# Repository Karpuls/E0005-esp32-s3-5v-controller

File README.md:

# E0005: ESP32-S3 5 V controller board

The 5 V version of the E0003 control-box mainboard. An **ESP32-S3** runs the box from a **2S1P 21700 pack** (Molicel P50B, holders on the bottom side), or from **plain 5 V USB-C (no PD)** with no cells fitted. One protected **5 V system rail (V5)** feeds the 3V3 regulator and five **+5 V peripheral ports**:
- 4 × fader driver (E0001 pinout);
- 1 × haptic knob (E0002 pinout).

Each port has its own eFuse and an I²C channel through a mux. The board also drives an **EYESPI SPI LCD** and reads **4 switch inputs**.

The current E0001 rev C and E0002 rev B need 6–9 V. They **will not run** on E0005: 5 V revisions are needed (SPEC §6 is their host-interface spec).

*Top side (KiCad 3D render):*
- *USB-C J11, the U_IN eFuse, the BQ25887 charger and the TPS56637 buck on the west side;*
- *the five JST-GH ports with their eFuses along the north edge;*
- *the ESP32-S3 module with its antenna keep-out at the east edge;*
- *switch inputs, power button, EYESPI and BOOT/RESET on the south edge.*

## Key specs
| | |
|---|---|
| Board | **Rev A**, 125 × 73 mm, R3 corners, 4 × M3 (Ø3.2 mm plated, 4 mm inset) |
| PCB | **4 layers, 1.6 mm**, 1 oz outer / 0.5 oz inner, JLC impedance stackup **JLC04161H-3313**. USB pair 90 Ω differential (W 0.153 / S 0.20 mm, coplanar, L1 over In1 GND) |
| Layers | **F.Cu**: parts, signals, power pours · **In1**: solid GND · **In2**: V5 plane (west column + port band), 3V3 plane, short slow lanes · **B.Cu**: signals, GND pour, holder lugs, V5 strap |
| MCU | **ESP32-S3-WROOM-1-N16R2** (16 MB flash, 2 MB PSRAM, Wi-Fi/BLE, PCB antenna) |
| Battery | **2 × Molicel P50B 21700 in series** (2S1P, ≈ 36 Wh), 2 × Keystone 1121 holders on the bottom |
| USB | **USB-C, 5 V only, no PD:** 2 × 5.1 kΩ Rd, CC1/CC2 to the ESP32 ADC to read the source's Rp level. Native USB for flashing, CDC and JTAG |
| Charger | **TI BQ25887** 2 A boost charger (5 V → 2S), I²C, 16-bit ADC, integrated cell balancing |
| 5 V rail (V5) | Diode-OR by voltage: **USB through a TPS259470A eFuse** (0.50 / 1.37 / 2.81 A limit, chosen by firmware) **or** the **TPS56637 6 A buck** from the pack (4.80 V). Copper is sized for 4.6 A at ΔT ≤ 20 °C |
| Ports | **6 × TPS259470A** eFuses in total: U_IN plus one per port J1–J5 (OVLO 6.0 V, UVLO 3.8 V, reverse blocking, auto-retry) |
| Status | DRC 0 errors / 0 unconnected / 0 parity (U1 library exception only), ERC 0. Fab outputs in `fab/E0005_revA/`. See "Status and open items" |

## Features and interfaces
| Function | Implementation |
|---|---|
| USB-C (J11) | ESP32-S3 native USB (flashing, CDC console, JTAG) and the charging input. Runs the whole system with no battery fitted. SMF9.0A TVS on VBUS, USBLC6 ESD on the data lines |
| Power path | **U_IN** (TPS259470A) feeds V5 from VBUS. Its limit is 0.50 A at reset, and 1.37 A or 2.81 A when firmware selects it from the CC level. When the load exceeds the USB limit, the **TPS56637** buck makes up the difference from the battery. U_IN blocks reverse current, so the buck never back-feeds the USB host |
| Charger | **BQ25887** 5 V → 2S boost charger, 2 A, balancing ≈ 110 mA, cell OVP, JEITA (NTCs RT1/RT2) |
| Battery management | **MAX17205** fuel gauge (5 mΩ sense, Kelvin) · **S-8252** 2S protector with 2 × PSMN2R0-30YLDX · **10 A fuse F1** · per-cell voltages from the BQ25887 ADC |
| 3V3 rail | TPS629210 1 A buck from V5, so a port fault never resets the MCU |
| Ports J1–J4 | 4 × E0001-pinout ports, JST-GH 4-pin (1 +5V, 2 SCL, 3 SDA, 4 GND), eFuse 0.74–1.00 A, SMF5.0A TVS |
| Port J5 | 1 × E0002-pinout port, JST-GH 6-pin (1–2 +5V, 3 SCL, 4 SDA, 5–6 GND), eFuse 1.80–2.20 A |
| I²C | **I2C0** on-board: BQ25887, MAX17205, TCA9535 expander. **I2C1**: PCA9548A mux, one channel per port, 3.3 V pull-ups, ESD and series resistors |
| LCD (J10) | 18-pin 0.5 mm **EYESPI** FPC for the Adafruit 2.0" 320×240 IPS (PID 4311) |
| Switch inputs (J6–J9) | 4 × JST-GH 2-pin, pull-up + RC + ESD, wake from deep sleep |
| Buttons | Power button (on board, plus JST-GH J12 for a panel button) with a **soft power latch on the buck EN** ("off" ≈ 35 µA); BOOT, RESET |
| Silkscreen | **"5V Jn E0001"** / **"5V J5 E0002"** at each port |
| Test points | None (owner rule). Bring-up is via USB and component pads |

## Power architecture
- **USB only:** V5 = VBUS through U_IN, at 4.9–5.1 V. The buck is off.
- **Battery only:** V5 = TPS56637 output, 4.80 V. Firmware sheds the ports below a 6.4 V pack.
- **USB + battery:** USB holds V5 above the buck set point, so the buck is idle. When the load exceeds U_IN's limit, U_IN regulates its current and the buck carries the rest. The charger charges the pack from VBUS at the same time; firmware keeps U_IN + charger input within the source's Rp budget.
- Load budget:
  - worst plausible V5 load 4.85 A;
  - firmware port budget 4.4 A;
  - TPS56637 rated 6 A, with a 6.3–8.6 A valley limit.
- Details: [`docs/SPEC.md`](docs/SPEC.md) §5.

## Copper layers
All four layers are seen from the top, with the board outline (KiCad plots).

| | |
|---|---|
|  *F.Cu: parts, signals, power pours* |  *In1.Cu: solid GND reference plane* |
|  *In2.Cu: V5 plane (west column, port band), 3V3 plane* |  *B.Cu: signals, GND pour, holder lugs, V5 strap* |

## More views
| | |
|---|---|
|  *Bottom side: the two Keystone 1121 holders* |  *Top mask and silk, rendered from the gerbers* |

## Repository layout
| Path | Content |
|---|---|
| `E0005_controller.kicad_pro` / `.kicad_pcb` / `.kicad_sch` | KiCad project, board and root schematic |
| `power.kicad_sch`, `battery.kicad_sch`, `mcu.kicad_sch`, `ports.kicad_sch` | Schematic sheets: USB-C, U_IN, charger, buck and 3V3 · battery pack, protection and gauge · ESP32-S3, LCD, switches, buttons · peripheral ports |
| `E0005_controller.kicad_dru` | JLC design rules, the no-via-on-pad rule, and the routing pour/USB rules |
| `docs/SPEC.md` | Requirements and architecture spec (v1.4, frozen) |
| `docs/schematic_notes.md`, `docs/placement_notes.md`, `docs/routing_notes.md` | Capture notes (deviations, V5 capacitance, back-feed), placement notes, routing notes (widths, IPC-2152 table, USB, hot loops) |
| `docs/images/` | Board and 3D renders used here |
| `bom/` | DigiKey BOM (`E0005_digikey_bom.csv`, generated), new-part lookups, sourcing notes |
| `lib/` | Project symbols and footprints (`E0005.*`), the board outline and holes (`E0005_board`), and mechanical parts with 3D models (`E0005_mech.*`) |
| `build/scripts/` | Generators and checks. **`fab_export.sh`** builds the fab package; **`gerber_review.py`** renders and measures the gerbers; `make_bom.py` builds the BOM |
| `build/route/` | Hand-routing scripts (sent over KiCad IPC; no autorouter) |
| `fab/E0005_revA/` | **Fabrication package:** `E0005_revA_gerbers_JLC.zip` (upload to JLC), gerbers, drill, placement, assembly PDFs, BOM, STEP, DRC/ERC reports, gerber review, [README](fab/E0005_revA/README.md) with the order settings, and [PREORDER.md](fab/E0005_revA/PREORDER.md) |

## Status and open items
- **Rev A fab outputs are generated:** DRC 0 / 0 / 0 (U1 `lib_footprint_mismatch` accepted), ERC 0. JLC order settings (JLC04161H-3313 with impedance control, tented vias, ENIG) are in [`fab/E0005_revA/README.md`](fab/E0005_revA/README.md).
- **Before ordering** ([`PREORDER.md`](fab/E0005_revA/PREORDER.md)):
  - Test-fit the flat-top P50B in the Keystone 1121.
  - Confirm the DigiKey cut-tape PNs for BQ25887RGER and TPS56637RPAR.
  - Order the LCSC / Adafruit / nkon parts.
- **Bench checks at bring-up:**
  - O-1: TPS56637 load step (FF C79 100 → 220 pF if it rings);
  - O-2b: TPS56637 temperature with the SW discharge active (USB only, no battery);
  - O-4: USB-unplug V5 dip at full load, and U_IN temperature in current limit.
- **Sister boards:** E0001 and E0002 need 5 V revisions to work on this board (out of scope here).

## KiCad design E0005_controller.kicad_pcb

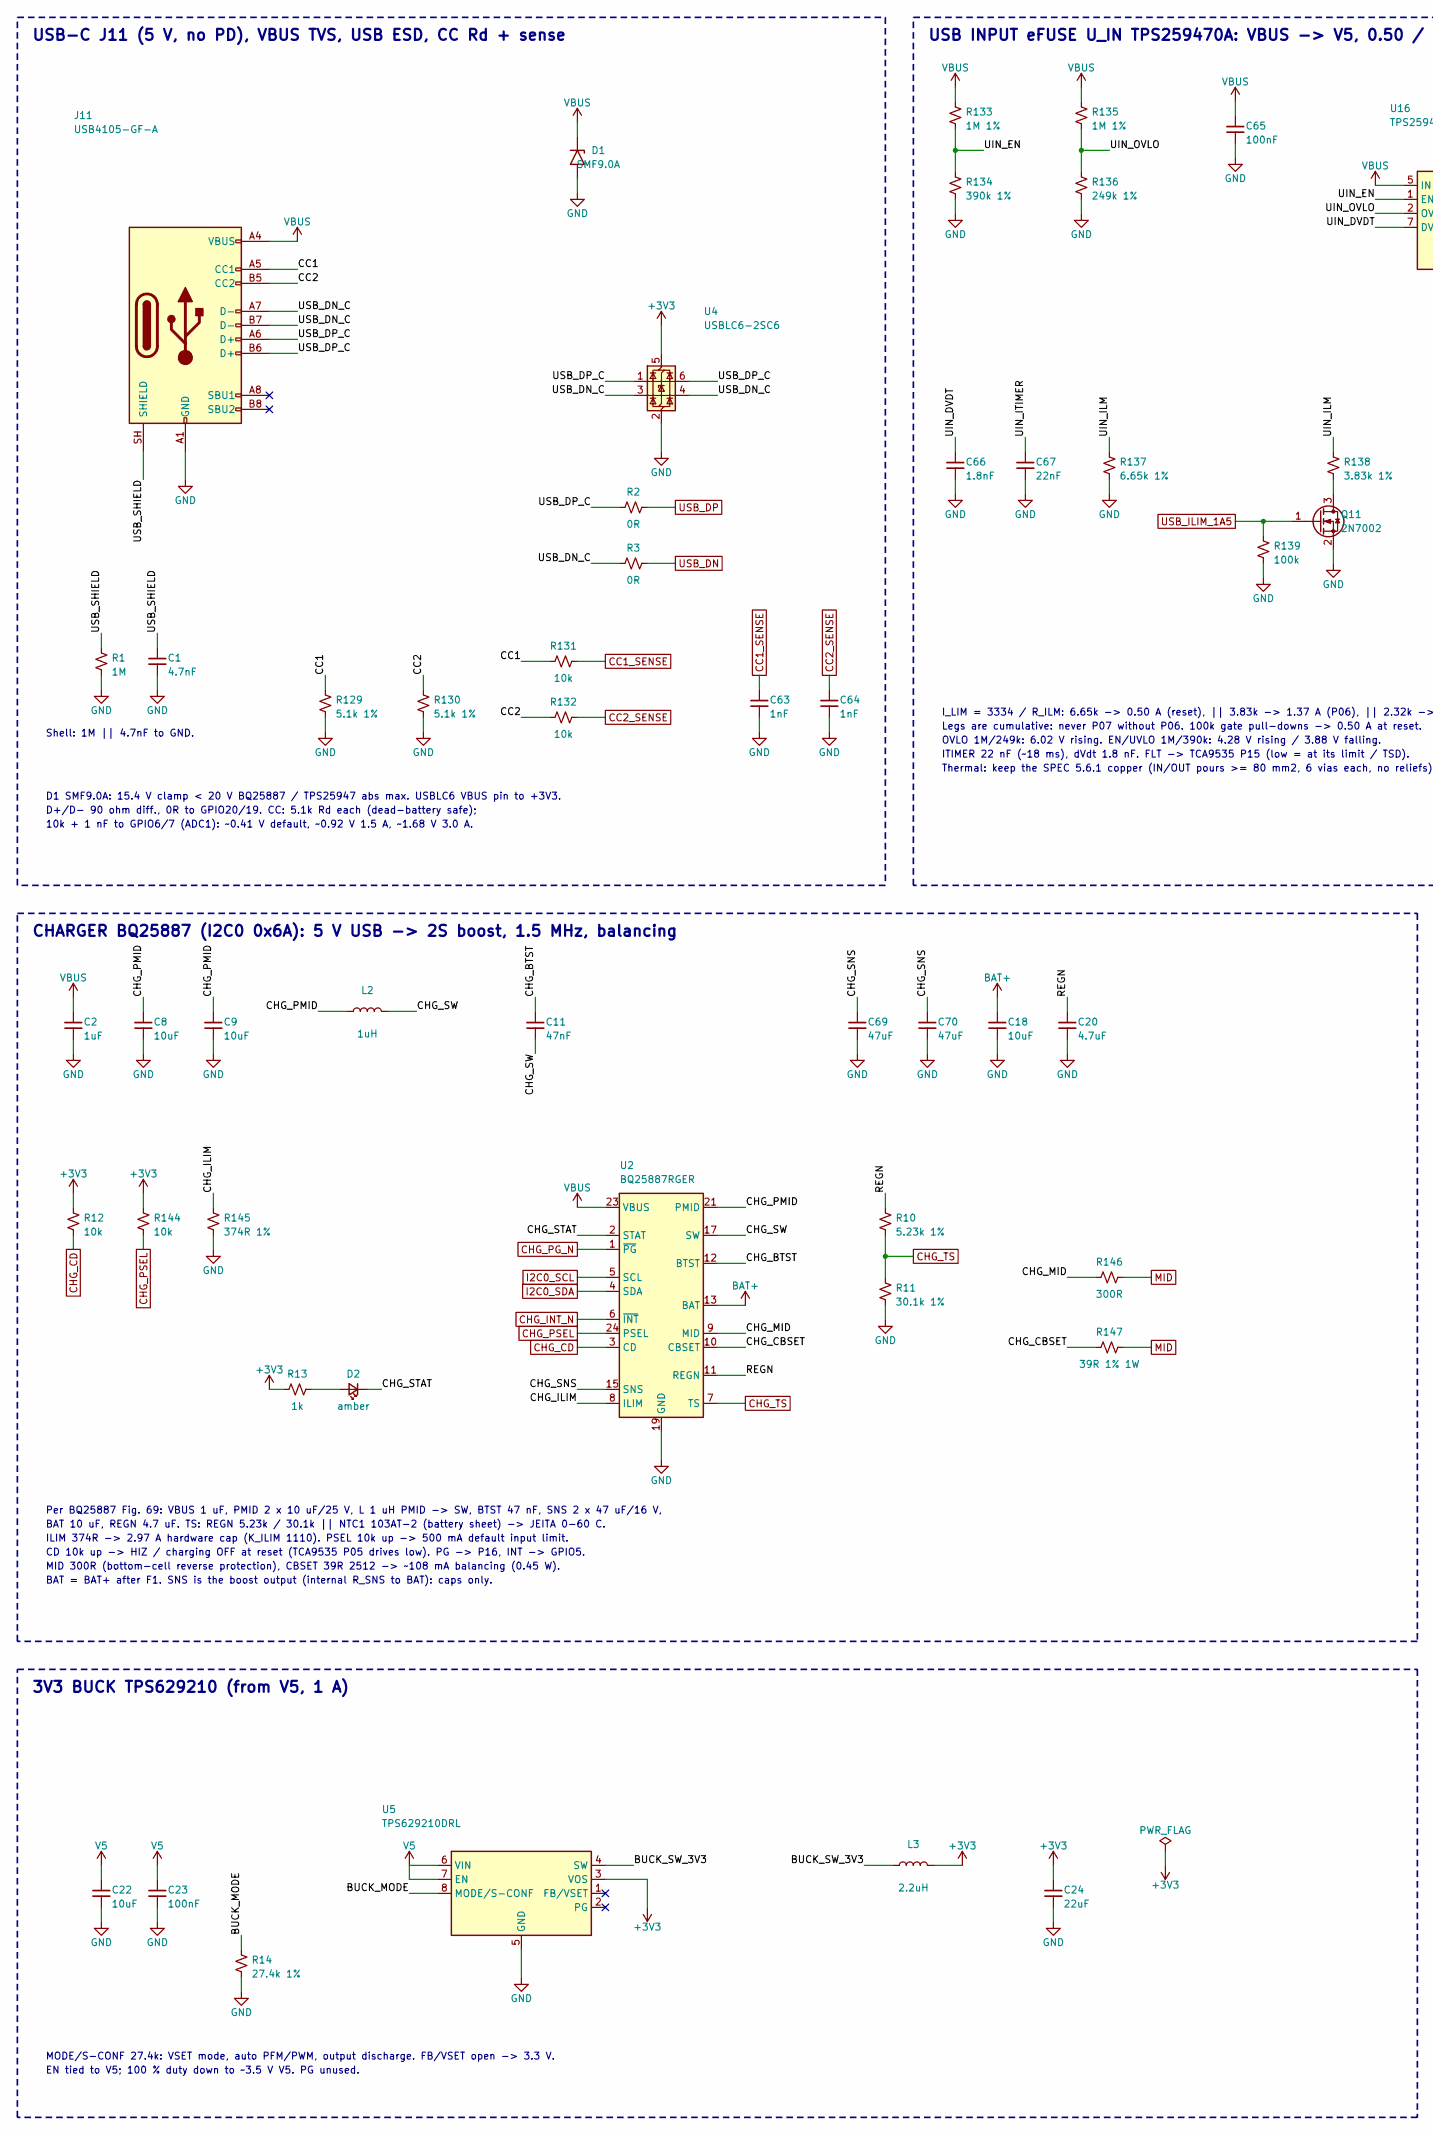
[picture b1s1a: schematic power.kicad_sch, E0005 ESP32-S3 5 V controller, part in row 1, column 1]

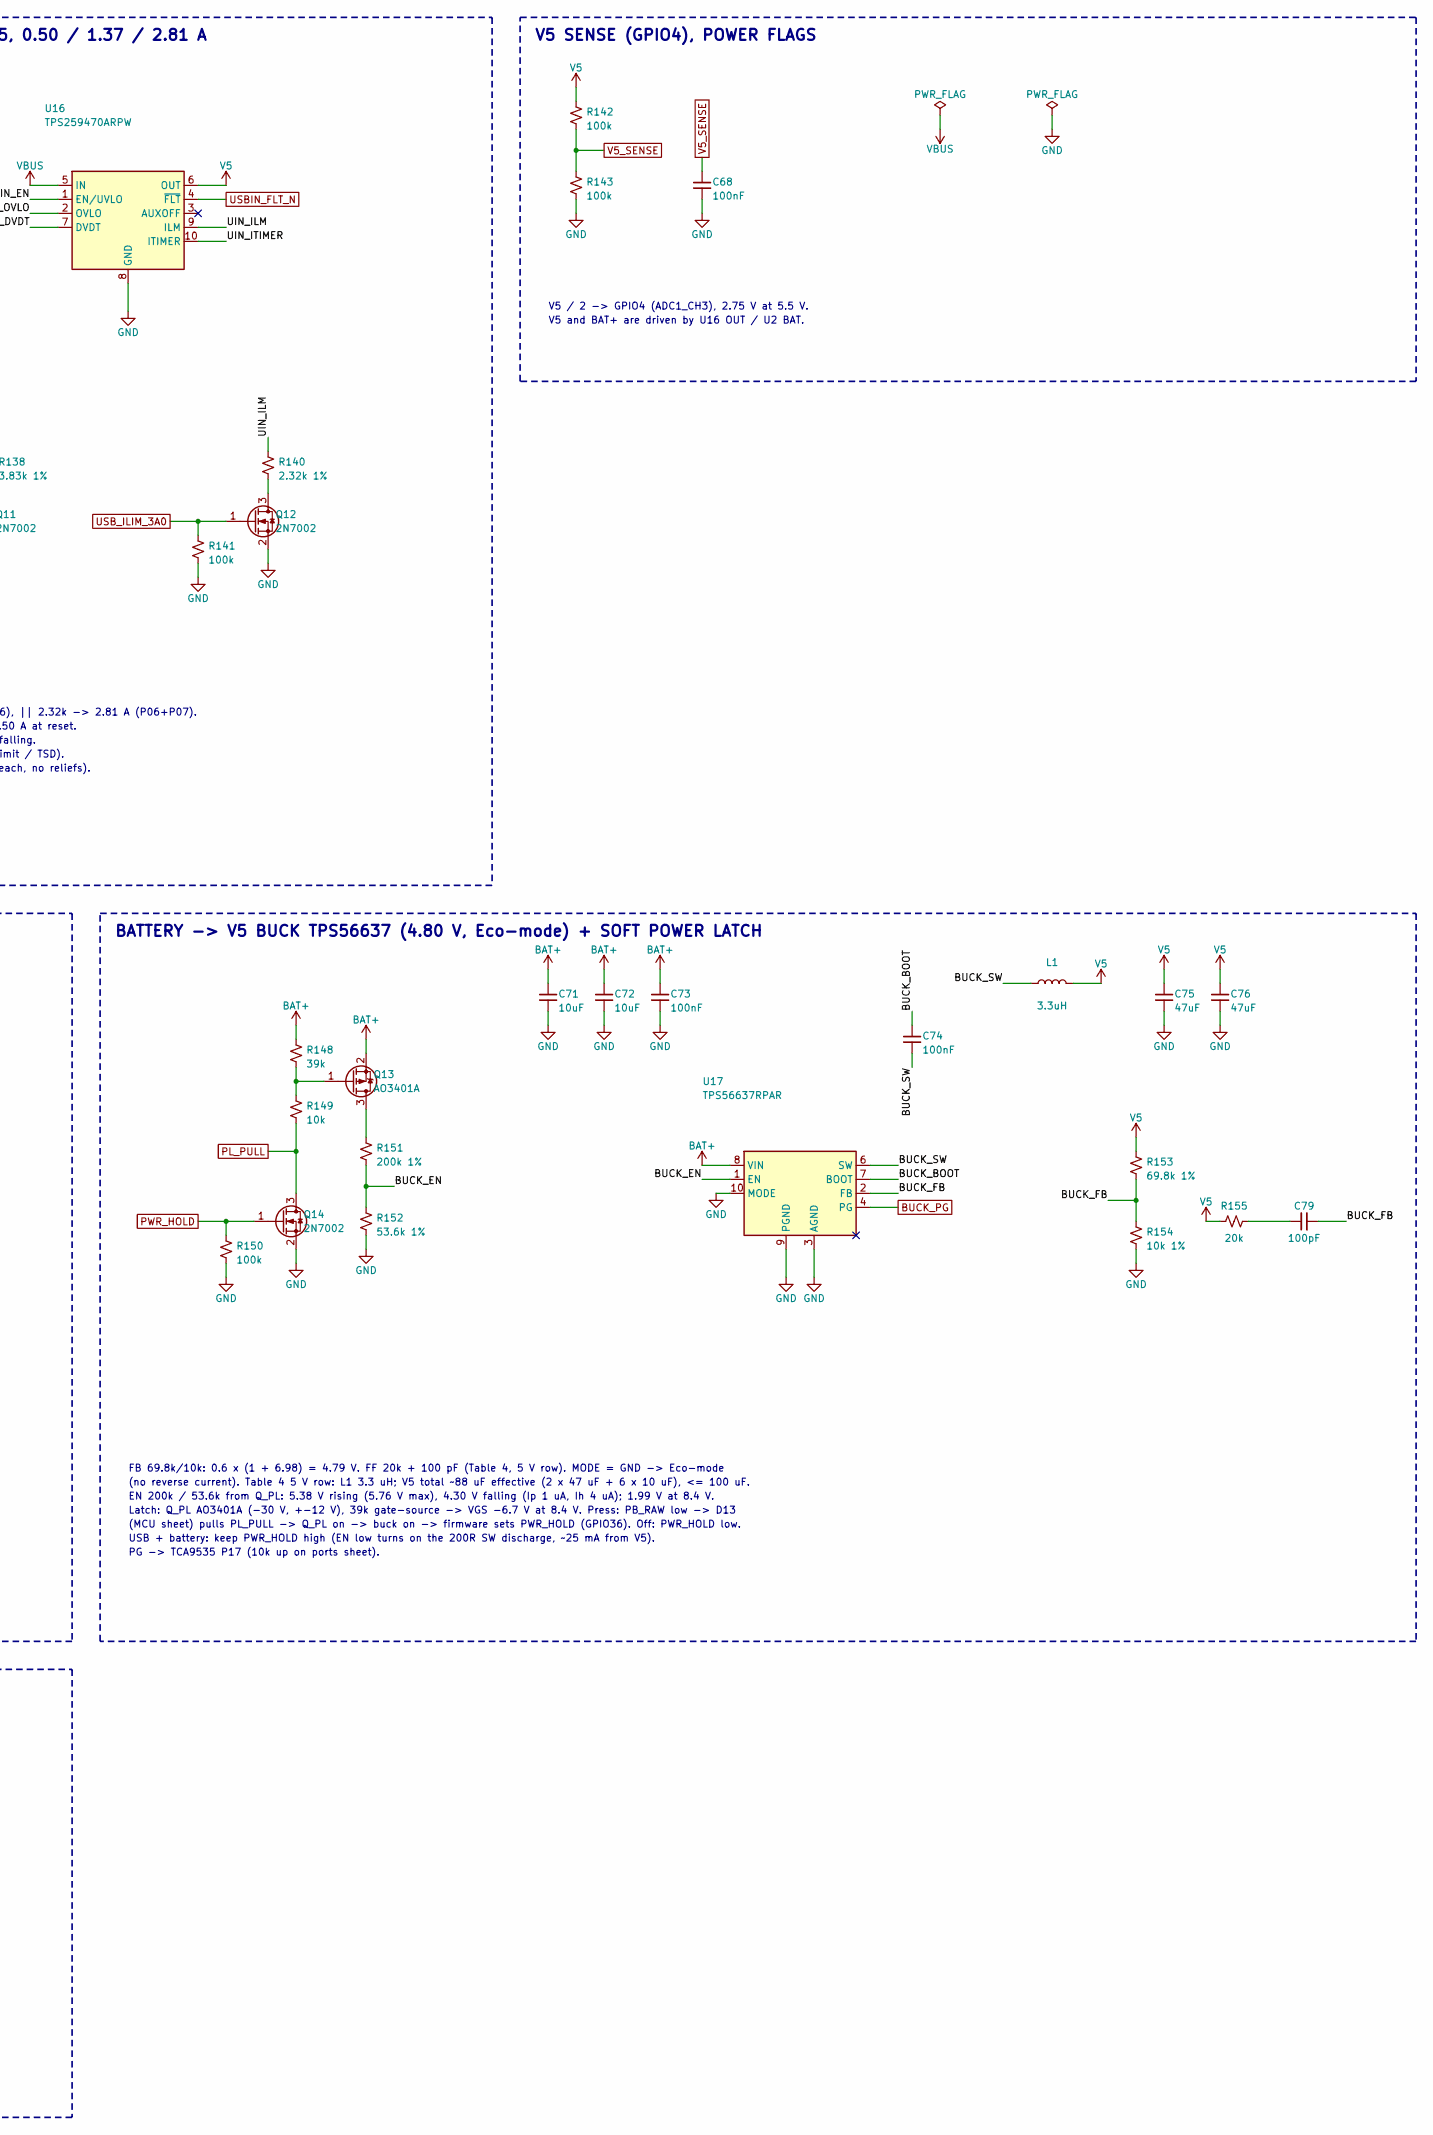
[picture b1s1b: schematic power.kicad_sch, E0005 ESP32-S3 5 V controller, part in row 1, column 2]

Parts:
C1: 4.7nF; C_0402_1005Metric; Voltage 50V; MPN GRM155R71H472KA01J
C2: 1uF; C_0603_1608Metric; Voltage 50V; MPN C1608X7R1H105K080AB
C8, C9, C18, C22, C71, C72: 10uF; C_0805_2012Metric; Voltage 25V; MPN TMK212BBJ106MG-T
C11: 47nF; C_0402_1005Metric; Voltage 50V; MPN GRM155R71H473KE14D
C20: 4.7uF; C_0603_1608Metric; Voltage 25V; MPN GRM188R61E475KE11D
C23, C65, C68, C73, C74: 100nF; C_0402_1005Metric; Voltage 50V; MPN GRM155R71H104KE14D
C24: 22uF; C_0805_2012Metric; Voltage 6.3V; MPN CL21A226KQCLRNC
C63, C64: 1nF; C_0402_1005Metric; MPN GRM155R71H102KA01D
C66: 1.8nF; C_0402_1005Metric; Voltage 50V; MPN C0402C182K5RACTU
C67: 22nF; C_0402_1005Metric; Voltage 50V; MPN GRM155R71H223KA12D
C69, C70, C75, C76: 47uF; C_1210_3225Metric; Voltage 16V; MPN CL32A476KOJNNNE
C79: 100pF; C_0402_1005Metric; MPN GRM1555C1H101JA01D
D1: SMF9.0A; D_SOD-123F; MPN SMF9.0A
D2: amber; LED_0603_1608Metric; MPN LTST-C191KSKT
J11: USB4105-GF-A; USB_C_Receptacle_GCT_USB4105-xx-A_16P_TopMnt_Horizontal; MPN USB4105-GF-A
L1: 3.3uH; L_Vishay_IHLP-3232; MPN IHLP3232DZER3R3M11
L2: 1uH; L_Vishay_IHLP-2525; MPN IHLP2525CZER1R0M01
L3: 2.2uH; L_1008_2520Metric; MPN DFE252012PD-2R2M=P2
Q11, Q12, Q14: 2N7002; SOT-23; MPN 2N7002-7-F
Q13: AO3401A; SOT-23; MPN AO3401A
R1: 1M; R_0402_1005Metric; MPN RC0402FR-071ML
R2, R3: 0R; R_0402_1005Metric; MPN RC0402JR-070RL
R10: 5.23k 1%; R_0402_1005Metric; MPN RC0402FR-075K23L
R11: 30.1k 1%; R_0402_1005Metric; MPN RC0402FR-0730K1L
R12, R131, R132, R144, R149: 10k; R_0402_1005Metric; MPN RC0402FR-0710KL
R13: 1k; R_0402_1005Metric; MPN RC0402FR-071KL
R14: 27.4k 1%; R_0402_1005Metric; MPN RC0402FR-0727K4L
R129, R130: 5.1k 1%; R_0402_1005Metric; MPN RC0402FR-075K1L
R133, R135: 1M 1%; R_0402_1005Metric; MPN RC0402FR-071ML
R134: 390k 1%; R_0402_1005Metric; MPN RC0402FR-07390KL
R136: 249k 1%; R_0402_1005Metric; MPN RC0402FR-07249KL
R137: 6.65k 1%; R_0402_1005Metric; MPN RC0402FR-076K65L
R138: 3.83k 1%; R_0402_1005Metric; MPN RC0402FR-073K83L
R139, R141, R142, R143, R150: 100k; R_0402_1005Metric; MPN RC0402FR-07100KL
R140: 2.32k 1%; R_0402_1005Metric; MPN RC0402FR-072K32L
R145: 374R 1%; R_0402_1005Metric; MPN RC0402FR-07374RL
R146: 300R; R_0402_1005Metric; MPN RC0402FR-07300RL
R147: 39R 1% 1W; R_2512_6332Metric; MPN RMCF2512FT39R0
R148: 39k; R_0402_1005Metric; MPN RC0402FR-0739KL
R151: 200k 1%; R_0402_1005Metric; MPN RC0402FR-07200KL
R152: 53.6k 1%; R_0402_1005Metric; MPN RC0402FR-0753K6L
R153: 69.8k 1%; R_0402_1005Metric; MPN RC0402FR-0769K8L
R154: 10k 1%; R_0402_1005Metric; MPN RC0402FR-0710KL
R155: 20k; R_0402_1005Metric; MPN RC0402FR-0720KL
U2: BQ25887RGER; Texas_RGE0024H_VQFN-24-1EP_4x4mm_P0.5mm_EP2.7x2.7mm; MPN BQ25887RGER
U4: USBLC6-2SC6; SOT-23-6; MPN USBLC6-2SC6
U5: TPS629210DRL; SOT-583-8; MPN TPS629210DRLR
U16: TPS259470ARPW; TI_RPW0010A_VQFN-HR-10_2x2mm_P0.475mm; MPN TPS259470ARPWR
U17: TPS56637RPAR; TI_RPA0010A_VQFN-HR-10_3x3mm; MPN TPS56637RPAR

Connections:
+3V3: C24.1, L3.2, R12.1, R13.1, R144.1, U4.5 (VBUS), U5.3 (VOS); also elsewhere on the board
/Power: USB-C, U_IN, charger, 5 V buck, 3V3/BUCK_BOOT: C74.1, U17.7 (BOOT)
/Power: USB-C, U_IN, charger, 5 V buck, 3V3/BUCK_EN: R151.2, R152.1, U17.1 (EN)
/Power: USB-C, U_IN, charger, 5 V buck, 3V3/BUCK_FB: C79.2, R153.2, R154.1, U17.2 (FB)
/Power: USB-C, U_IN, charger, 5 V buck, 3V3/BUCK_MODE: R14.1, U5.8 (MODE/S-CONF)
/Power: USB-C, U_IN, charger, 5 V buck, 3V3/BUCK_SW: C74.2, L1.1, U17.6 (SW)
/Power: USB-C, U_IN, charger, 5 V buck, 3V3/BUCK_SW_3V3: L3.1, U5.4 (SW)
/Power: USB-C, U_IN, charger, 5 V buck, 3V3/CC1: J11.A5 (CC1), R129.1, R131.1
/Power: USB-C, U_IN, charger, 5 V buck, 3V3/CC2: J11.B5 (CC2), R130.1, R132.1
/Power: USB-C, U_IN, charger, 5 V buck, 3V3/CHG_BTST: C11.1, U2.12 (BTST)
/Power: USB-C, U_IN, charger, 5 V buck, 3V3/CHG_CBSET: R147.1, U2.10 (CBSET)
/Power: USB-C, U_IN, charger, 5 V buck, 3V3/CHG_ILIM: R145.1, U2.8 (ILIM)
/Power: USB-C, U_IN, charger, 5 V buck, 3V3/CHG_MID: R146.1, U2.9 (MID)
/Power: USB-C, U_IN, charger, 5 V buck, 3V3/CHG_PMID: C8.1, C9.1, L2.1, U2.21 (PMID), U2.22 (PMID)
/Power: USB-C, U_IN, charger, 5 V buck, 3V3/CHG_SNS: C69.1, C70.1, U2.15 (SNS), U2.16 (SNS)
/Power: USB-C, U_IN, charger, 5 V buck, 3V3/CHG_STAT: D2.1 (K), U2.2 (STAT)
/Power: USB-C, U_IN, charger, 5 V buck, 3V3/CHG_SW: C11.2, L2.2, U2.17 (SW), U2.18 (SW)
/Power: USB-C, U_IN, charger, 5 V buck, 3V3/REGN: C20.1, R10.1, U2.11 (REGN)
/Power: USB-C, U_IN, charger, 5 V buck, 3V3/UIN_DVDT: C66.1, U16.7 (DVDT)
/Power: USB-C, U_IN, charger, 5 V buck, 3V3/UIN_EN: R133.2, R134.1, U16.1 (EN/UVLO)
/Power: USB-C, U_IN, charger, 5 V buck, 3V3/UIN_ILM: R137.1, R138.1, R140.1, U16.9 (ILM)
/Power: USB-C, U_IN, charger, 5 V buck, 3V3/UIN_ITIMER: C67.1, U16.10 (ITIMER)
/Power: USB-C, U_IN, charger, 5 V buck, 3V3/UIN_OVLO: R135.2, R136.1, U16.2 (OVLO)
/Power: USB-C, U_IN, charger, 5 V buck, 3V3/USB_DN_C: J11.A7 (D-), J11.B7 (D-), R3.1, U4.3 (I/O2), U4.4 (I/O2)
/Power: USB-C, U_IN, charger, 5 V buck, 3V3/USB_DP_C: J11.A6 (D+), J11.B6 (D+), R2.1, U4.1 (I/O1), U4.6 (I/O1)
/Power: USB-C, U_IN, charger, 5 V buck, 3V3/USB_SHIELD: C1.1, J11.SH (SHIELD), R1.1
BAT+: C18.1, C71.1, C72.1, C73.1, Q13.2 (S), R148.1, U2.13 (BAT), U2.14 (BAT), U17.8 (VIN); also elsewhere on the board
BUCK_PG: U17.4 (PG); also elsewhere on the board
CC1_SENSE: C63.1, R131.2; also elsewhere on the board
CC2_SENSE: C64.1, R132.2; also elsewhere on the board
CHG_CD: R12.2, U2.3 (CD); also elsewhere on the board
CHG_INT_N: U2.6 (~INT); also elsewhere on the board
CHG_PG_N: U2.1 (~PG); also elsewhere on the board
CHG_PSEL: R144.2, U2.24 (PSEL)
CHG_TS: R10.2, R11.1, U2.7 (TS); also elsewhere on the board
GND: C1.2, C2.2, C8.2, C9.2, C18.2, C20.2, C22.2, C23.2, C24.2, C63.2, C64.2, C65.2, C66.2, C67.2, C68.2, C69.2, C70.2, C71.2, C72.2, C73.2, C75.2, C76.2, D1.2 (A2), J11.A1 (GND), J11.A12 (GND), J11.B1 (GND), J11.B12 (GND), Q11.2 (S), Q12.2 (S), Q14.2 (S), R1.2, R11.2, R14.2, R129.2, R130.2, R134.2, R136.2, R137.2, R139.2, R141.2, R143.2, R145.2, R150.2, R152.2, R154.2, U2.19 (GND), U2.20 (GND), U2.25 (GND), U4.2 (GND), U5.5 (GND), U16.8 (GND), U17.3 (AGND), U17.9 (PGND), U17.10 (MODE); also elsewhere on the board
I2C0_SCL: U2.5 (SCL); also elsewhere on the board
I2C0_SDA: U2.4 (SDA); also elsewhere on the board
MID: R146.2, R147.2; also elsewhere on the board
unnamed: C79.1, R155.2
unnamed: D2.2 (A), R13.2
unnamed: Q11.3 (D), R138.2
unnamed: Q12.3 (D), R140.2
unnamed: Q13.3 (D), R151.1
unnamed: Q13.1 (G), R148.2, R149.1
PL_PULL: Q14.3 (D), R149.2; also elsewhere on the board
PWR_HOLD: Q14.1 (G), R150.1; also elsewhere on the board
USBIN_FLT_N: U16.4 (~FLT); also elsewhere on the board
USB_DN: R3.2; also elsewhere on the board
USB_DP: R2.2; also elsewhere on the board
USB_ILIM_1A5: Q11.1 (G), R139.1; also elsewhere on the board
USB_ILIM_3A0: Q12.1 (G), R141.1; also elsewhere on the board
V5: C22.1, C23.1, C75.1, C76.1, L1.2, R142.1, R153.1, R155.1, U5.6 (VIN), U5.7 (EN), U16.6 (OUT); also elsewhere on the board
V5_SENSE: C68.1, R142.2, R143.1; also elsewhere on the board
VBUS: C2.1, C65.1, D1.1 (A1), J11.A4 (VBUS), J11.A9 (VBUS), J11.B4 (VBUS), J11.B9 (VBUS), R133.1, R135.1, U2.23 (VBUS), U16.5 (IN)

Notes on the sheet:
USB-C J11 (5 V, no PD), VBUS TVS, USB ESD, CC Rd + sense
Shell: 1M || 4.7nF to GND.
D1 SMF9.0A: 15.4 V clamp < 20 V BQ25887 / TPS25947 abs max. USBLC6 VBUS pin to +3V3.
D+/D- 90 ohm diff., 0R to GPIO20/19. CC: 5.1k Rd each (dead-battery safe);
10k + 1 nF to GPIO6/7 (ADC1): ~0.41 V default, ~0.92 V 1.5 A, ~1.68 V 3.0 A.
USB INPUT eFUSE U_IN TPS259470A: VBUS -> V5, 0.50 / 1.37 / 2.81 A
I_LIM = 3334 / R_ILM: 6.65k -> 0.50 A (reset), || 3.83k -> 1.37 A (P06), || 2.32k -> 2.81 A (P06+P07).
Legs are cumulative: never P07 without P06. 100k gate pull-downs -> 0.50 A at reset.
OVLO 1M/249k: 6.02 V rising. EN/UVLO 1M/390k: 4.28 V rising / 3.88 V falling.
ITIMER 22 nF (~18 ms), dVdt 1.8 nF. FLT -> TCA9535 P15 (low = at its limit / TSD).
Thermal: keep the SPEC 5.6.1 copper (IN/OUT pours >= 80 mm2, 6 vias each, no reliefs).
V5 SENSE (GPIO4), POWER FLAGS
V5 / 2 -> GPIO4 (ADC1_CH3), 2.75 V at 5.5 V.
V5 and BAT+ are driven by U16 OUT / U2 BAT.
CHARGER BQ25887 (I2C0 0x6A): 5 V USB -> 2S boost, 1.5 MHz, balancing
Per BQ25887 Fig. 69: VBUS 1 uF, PMID 2 x 10 uF/25 V, L 1 uH PMID -> SW, BTST 47 nF, SNS 2 x 47 uF/16 V,
BAT 10 uF, REGN 4.7 uF. TS: REGN 5.23k / 30.1k || NTC1 103AT-2 (battery sheet) -> JEITA 0-60 C.
ILIM 374R -> 2.97 A hardware cap (K_ILIM 1110). PSEL 10k up -> 500 mA default input limit.
CD 10k up -> HIZ / charging OFF at reset (TCA9535 P05 drives low). PG -> P16, INT -> GPIO5.
MID 300R (bottom-cell reverse protection), CBSET 39R 2512 -> ~108 mA balancing (0.45 W).
BAT = BAT+ after F1. SNS is the boost output (internal R_SNS to BAT): caps only.
BATTERY -> V5 BUCK TPS56637 (4.80 V, Eco-mode) + SOFT POWER LATCH
FB 69.8k/10k: 0.6 x (1 + 6.98) = 4.79 V. FF 20k + 100 pF (Table 4, 5 V row). MODE = GND -> Eco-mode
(no reverse current). Table 4 5 V row: L1 3.3 uH; V5 total ~88 uF effective (2 x 47 uF + 6 x 10 uF), <= 100 uF.
EN 200k / 53.6k from Q_PL: 5.38 V rising (5.76 V max), 4.30 V falling (Ip 1 uA, Ih 4 uA); 1.99 V at 8.4 V.
Latch: Q_PL AO3401A (-30 V, +-12 V), 39k gate-source -> VGS -6.7 V at 8.4 V. Press: PB_RAW low -> D13
(MCU sheet) pulls PL_PULL -> Q_PL on -> buck on -> firmware sets PWR_HOLD (GPIO36). Off: PWR_HOLD low.
USB + battery: keep PWR_HOLD high (EN low turns on the 200R SW discharge, ~25 mA from V5).
PG -> TCA9535 P17 (10k up on ports sheet).
3V3 BUCK TPS629210 (from V5, 1 A)
MODE/S-CONF 27.4k: VSET mode, auto PFM/PWM, output discharge. FB/VSET open -> 3.3 V.
EN tied to V5; 100 % duty down to ~3.5 V V5. PG unused.

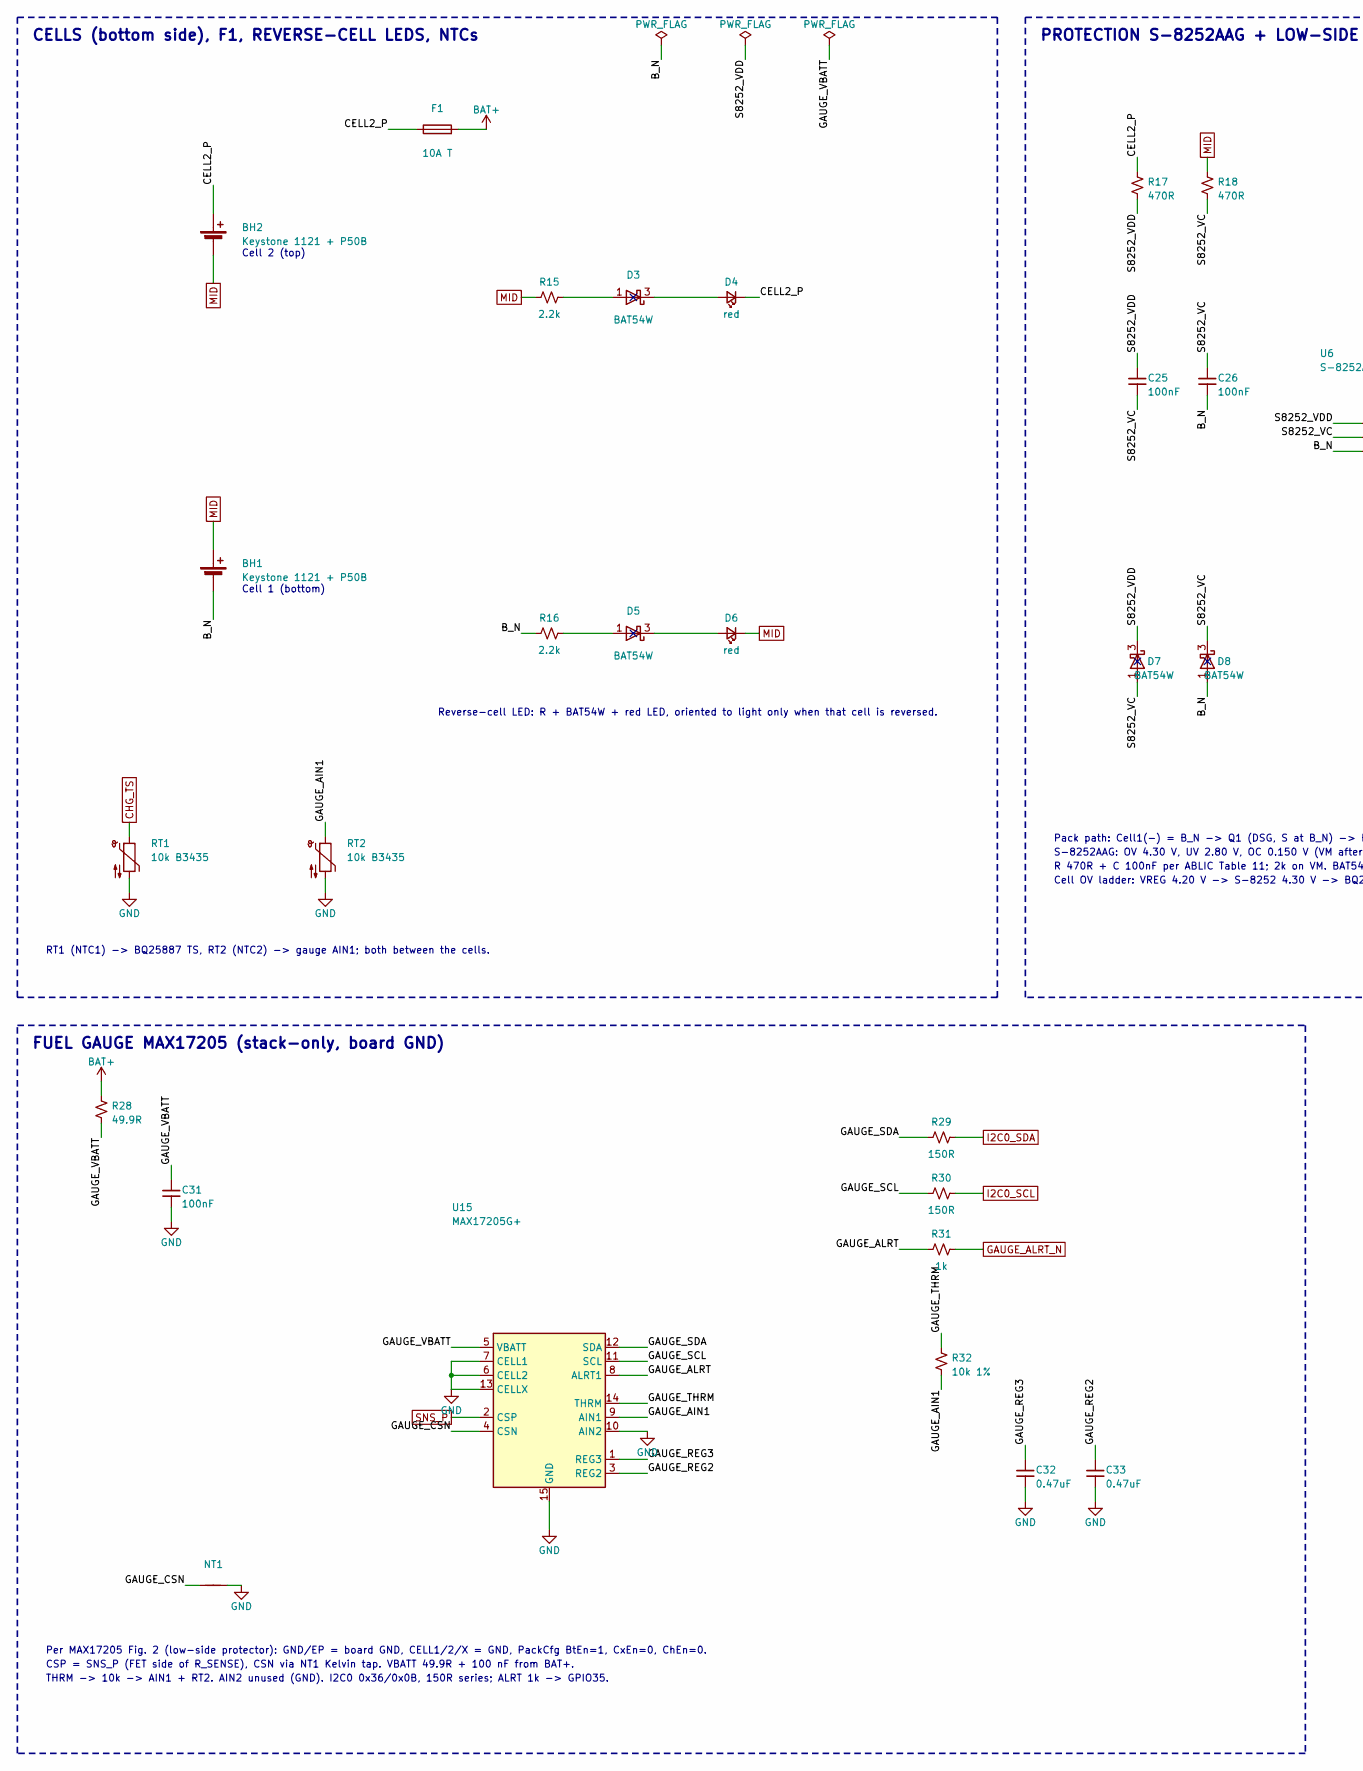
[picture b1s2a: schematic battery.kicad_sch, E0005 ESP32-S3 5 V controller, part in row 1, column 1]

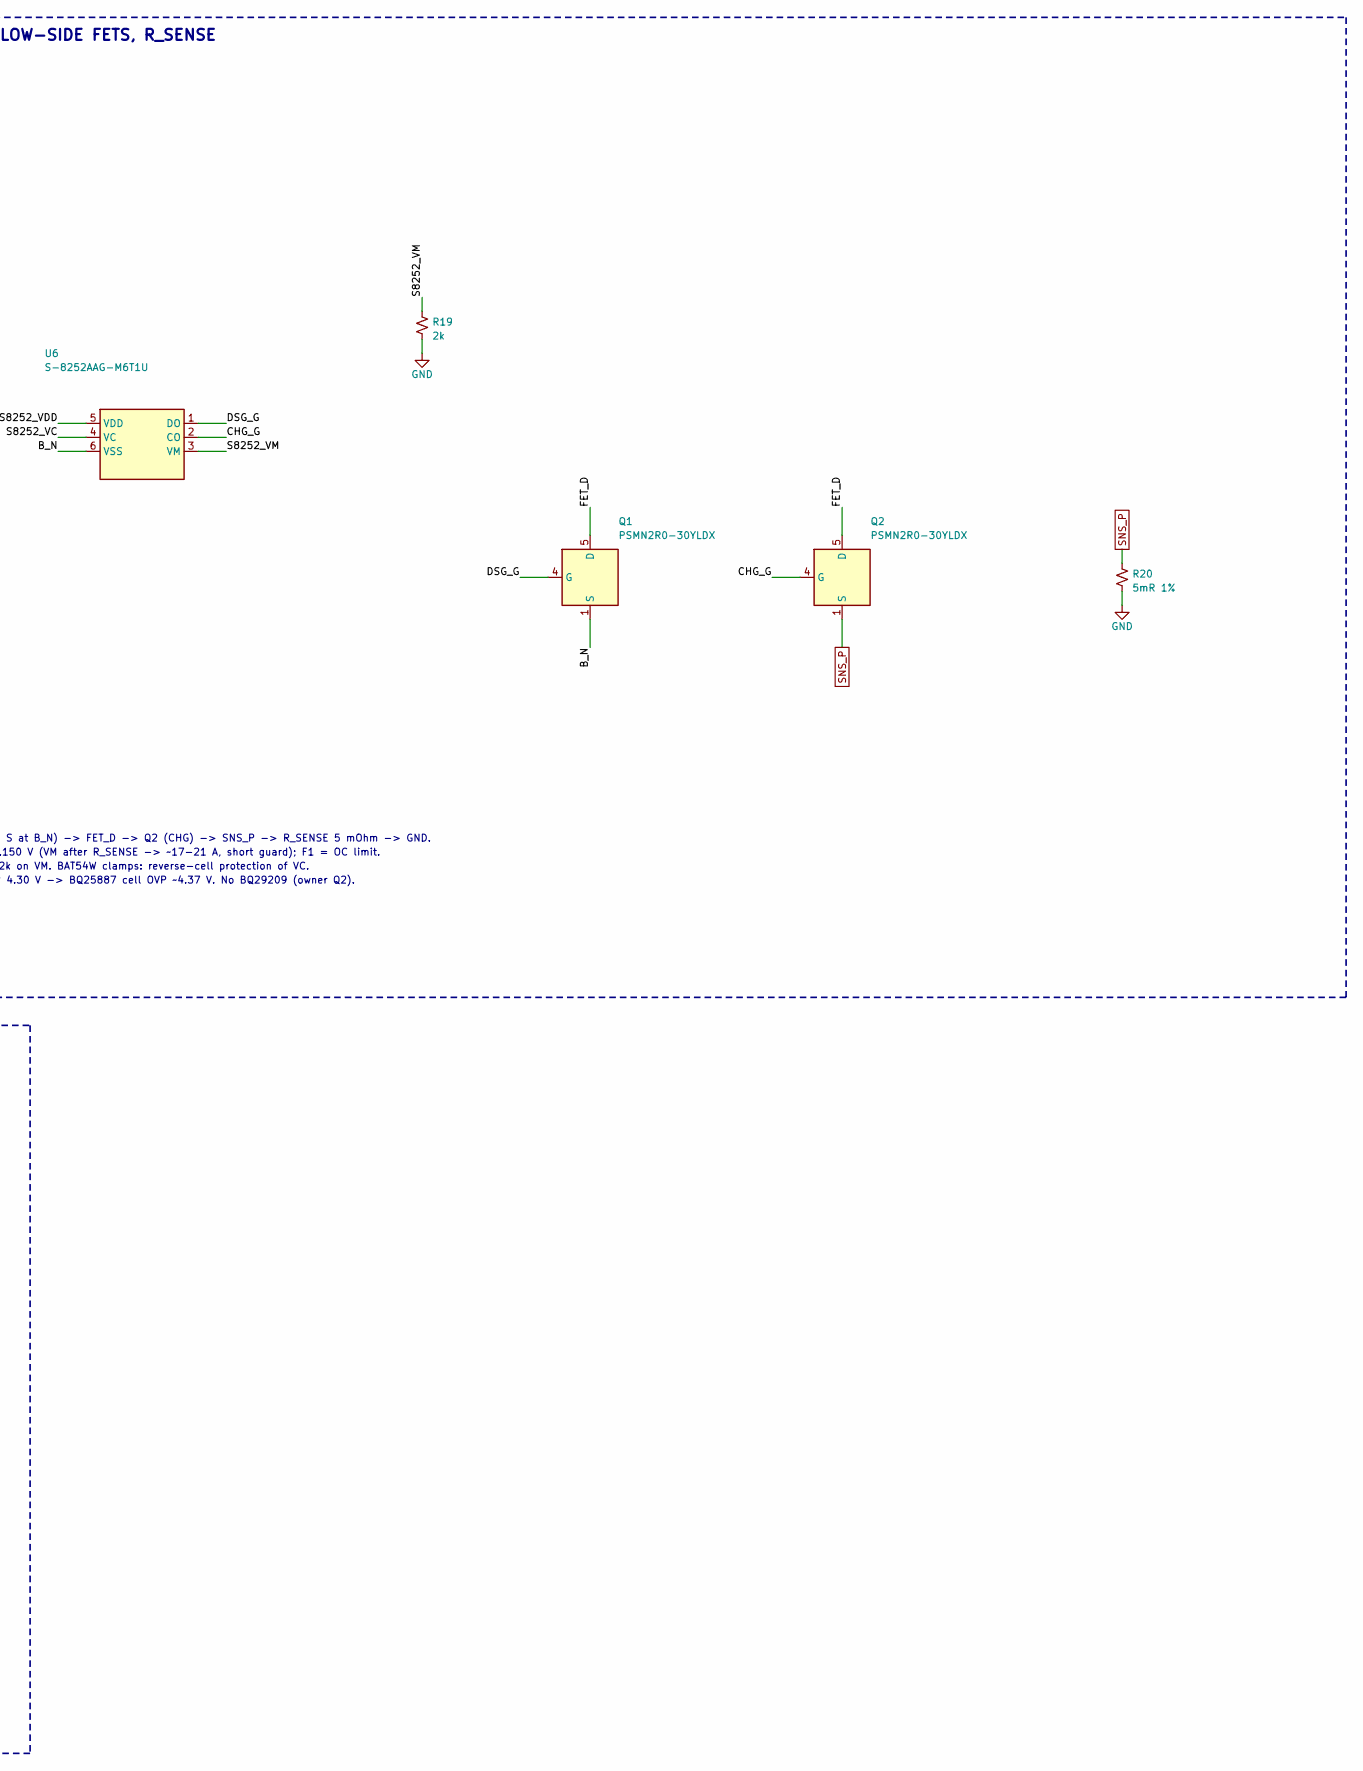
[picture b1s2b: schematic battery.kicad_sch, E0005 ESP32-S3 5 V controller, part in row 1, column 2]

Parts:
BH1, BH2: Keystone 1121 + P50B; Keystone_1121_1x21700_THM; MPN 1121
C25, C26, C31: 100nF; C_0402_1005Metric; Voltage 50V; MPN GRM155R71H104KE14D
C32, C33: 0.47uF; C_0402_1005Metric; MPN GRM155R61A474KE15D
D3, D5, D7, D8: BAT54W; SOT-323_SC-70; MPN BAT54W,135
D4, D6: red; LED_0603_1608Metric; MPN LTST-C191KRKT
F1: 10A T; Fuse_Littelfuse-NANO2-451_453; MPN 0452010.MRL
NT1: NetTie_2; NetTie-2_SMD_Pad0.5mm
Q1, Q2: PSMN2R0-30YLDX; LFPAK56; MPN PSMN2R0-30YLDX
R15, R16: 2.2k; R_0402_1005Metric; MPN RC0402FR-072K2L
R17, R18: 470R; R_0402_1005Metric; MPN RC0402FR-07470RL
R19: 2k; R_0402_1005Metric; MPN RK73H1ETTP2001F
R20: 5mR 1%; R_2512_6332Metric; MPN CRF2512-FZ-R005ELF
R28: 49.9R; R_0402_1005Metric; MPN RC0402FR-0749R9L
R29, R30: 150R; R_0402_1005Metric; MPN RC0402FR-07150RL
R31: 1k; R_0402_1005Metric; MPN RC0402FR-071KL
R32: 10k 1%; R_0402_1005Metric; MPN RC0402FR-0710KL
RT1, RT2: 10k B3435; NTC_Leaded_THT_P2.54mm_Drill0.8mm; MPN 103AT-2
U6: S-8252AAG-M6T1U; SOT-23-6; MPN S-8252AAG-M6T1U
U15: MAX17205G+; TDFN-14-1EP_3x3mm_P0.4mm_EP1.78x2.35mm; MPN MAX17205G+T

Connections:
/Battery pack, protection, gauge/B_N: BH1.2 (-), C26.2, D8.1 (A), Q1.1 (S), Q1.2 (S), Q1.3 (S), R16.1, U6.6 (VSS)
/Battery pack, protection, gauge/CELL2_P: BH2.1 (+), D4.1 (K), F1.1, R17.1
/Battery pack, protection, gauge/CHG_G: Q2.4 (G), U6.2 (CO)
/Battery pack, protection, gauge/DSG_G: Q1.4 (G), U6.1 (DO)
/Battery pack, protection, gauge/FET_D: Q1.5 (D), Q2.5 (D)
/Battery pack, protection, gauge/GAUGE_AIN1: R32.2, RT2.1, U15.9 (AIN1)
/Battery pack, protection, gauge/GAUGE_ALRT: R31.1, U15.8 (ALRT1)
/Battery pack, protection, gauge/GAUGE_CSN: NT1.1, U15.4 (CSN)
/Battery pack, protection, gauge/GAUGE_REG2: C33.1, U15.3 (REG2)
/Battery pack, protection, gauge/GAUGE_REG3: C32.1, U15.1 (REG3)
/Battery pack, protection, gauge/GAUGE_SCL: R30.1, U15.11 (SCL)
/Battery pack, protection, gauge/GAUGE_SDA: R29.1, U15.12 (SDA)
/Battery pack, protection, gauge/GAUGE_THRM: R32.1, U15.14 (THRM)
/Battery pack, protection, gauge/GAUGE_VBATT: C31.1, R28.2, U15.5 (VBATT)
/Battery pack, protection, gauge/S8252_VC: C25.2, C26.1, D7.1 (A), D8.3 (K), R18.2, U6.4 (VC)
/Battery pack, protection, gauge/S8252_VDD: C25.1, D7.3 (K), R17.2, U6.5 (VDD)
/Battery pack, protection, gauge/S8252_VM: R19.1, U6.3 (VM)
BAT+: F1.2, R28.1; also elsewhere on the board
CHG_TS: RT1.1; also elsewhere on the board
GAUGE_ALRT_N: R31.2; also elsewhere on the board
GND: C31.2, C32.2, C33.2, NT1.2, R19.2, R20.2, RT1.2, RT2.2, U15.6 (CELL2), U15.7 (CELL1), U15.10 (AIN2), U15.13 (CELLX), U15.15 (GND); also elsewhere on the board
I2C0_SCL: R30.2; also elsewhere on the board
I2C0_SDA: R29.2; also elsewhere on the board
MID: BH1.1 (+), BH2.2 (-), D6.1 (K), R15.1, R18.1; also elsewhere on the board
unnamed: D3.1 (A), R15.2
unnamed: D3.3 (K), D4.2 (A)
unnamed: D5.1 (A), R16.2
unnamed: D5.3 (K), D6.2 (A)
SNS_P: Q2.1 (S), Q2.2 (S), Q2.3 (S), R20.1, U15.2 (CSP)

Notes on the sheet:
CELLS (bottom side), F1, REVERSE-CELL LEDS, NTCs
Cell 2 (top)
Cell 1 (bottom)
Reverse-cell LED: R + BAT54W + red LED, oriented to light only when that cell is reversed.
RT1 (NTC1) -> BQ25887 TS, RT2 (NTC2) -> gauge AIN1; both between the cells.
PROTECTION S-8252AAG + LOW-SIDE FETS, R_SENSE
Pack path: Cell1(-) = B_N -> Q1 (DSG, S at B_N) -> FET_D -> Q2 (CHG) -> SNS_P -> R_SENSE 5 mOhm -> GND.
S-8252AAG: OV 4.30 V, UV 2.80 V, OC 0.150 V (VM after R_SENSE -> ~17-21 A, short guard); F1 = OC limit.
R 470R + C 100nF per ABLIC Table 11; 2k on VM. BAT54W clamps: reverse-cell protection of VC.
Cell OV ladder: VREG 4.20 V -> S-8252 4.30 V -> BQ25887 cell OVP ~4.37 V. No BQ29209 (owner Q2).
FUEL GAUGE MAX17205 (stack-only, board GND)
Per MAX17205 Fig. 2 (low-side protector): GND/EP = board GND, CELL1/2/X = GND, PackCfg BtEn=1, CxEn=0, ChEn=0.
CSP = SNS_P (FET side of R_SENSE), CSN via NT1 Kelvin tap. VBATT 49.9R + 100 nF from BAT+.
THRM -> 10k -> AIN1 + RT2. AIN2 unused (GND). I2C0 0x36/0x0B, 150R series; ALRT 1k -> GPIO35.
